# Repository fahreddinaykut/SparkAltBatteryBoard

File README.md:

# SparkAltBatteryBoard

A custom research-oriented battery interface and telemetry board for the DJI Spark platform, built around a standard 3S LiPo battery pack instead of the discontinued, hard-to-find OEM Smart Battery.

This project documents a reverse-engineered I2C/SMBus smart-battery communication interface, originally developed to study how the DJI Spark flight controller communicates with its battery pack. The board sits between a standard 3S pack and the drone, reads the real cell voltages and current, and reproduces that communication interface.

## How it works

1. The original DJI Spark Smart Battery was disassembled and its I2C/SMBus traffic with the flight controller was captured with a Saleae Logic Analyzer.
2. That traffic was decoded to recover the SBS + DJI-proprietary command set (auth handshake, cell voltages, PEC/CRC-8, etc.) — see [`Docs/I2C_BMS_PROTOCOL.md`](Docs/I2C_BMS_PROTOCOL.md).
3. A custom PCB replicates the OEM battery's form factor and connector, with resistor dividers for per-cell voltage sensing and an INA199 current shunt amplifier.
4. An ATmega328P on the board reproduces the Smart Battery communication interface over I2C in real time — computing PEC on the fly and clock-stretching where needed. See [`Firmware/README.md`](Firmware/README.md) for the full protocol implementation.

## Repository structure

| Folder | Contents |
|---|---|
| [`Hardware/`](Hardware) | KiCad project: schematics, PCB layout, 3D connector models, Gerbers, BOM |
| [`Firmware/`](Firmware) | PlatformIO project for the ATmega328P I2C/SMBus battery emulator |
| [`Mechanical/`](Mechanical) | Battery mount 3D model (STEP) |
| [`Docs/`](Docs) | Schematic PDF, protocol reverse-engineering notes, raw sniffed I2C sessions, reference photos/video |

## Hardware

| Top | Bottom | Layout |
|---|---|---|
|  |  |  |

- **MCU:** ATmega328P — chosen specifically because its hardware TWI peripheral supports I2C clock stretching reliably, which the DJI FC's polling requires (see [`Firmware/README.md`](Firmware/README.md#hardware) for why an ESP32 doesn't work here).
- **Sensing:** 3-way resistor divider network for per-cell voltage taps, INA199 shunt amplifier for pack current.
- **Full schematic:** [`Docs/SparkAltBatteryBoardV1.pdf`](Docs/SparkAltBatteryBoardV1.pdf)
- **Fabrication outputs:** [BOM](Hardware/Fabrication/SparkAltBatteryBoard_BOM.csv) · [Gerbers](Hardware/Fabrication/SparkAltBatteryBoard_Gerbers.zip)
- **Battery mount:** [`Mechanical/batterymount.stp`](Mechanical/batterymount.stp)

### PCB Design / Manufacturing Notes

The PCB revision was prepared as a manufacturing-oriented KiCad project, not only as a proof-of-concept schematic.

Design considerations include:

- Hierarchical schematic structure
- Separated MCU, power, sensing, and connector blocks
- 3.3 V I2C/SMBus logic interface
- ADC-scaled cell-voltage sensing inputs
- RC filtering on analog measurement lines
- INA199 high-side current-sense frontend
- Kelvin-style shunt measurement routing approach
- Buck-regulated 3.3 V system rail
- I2C pull-up resistors
- ESD/TVS protection on external communication lines
- AVR ICSP programming/debug header
- Wide copper routing/polygon strategy for battery current path
- Manufacturing outputs prepared: BOM and Gerber package

## Firmware

PlatformIO project targeting the ATmega328P (Arduino Uno/Nano pinout). Handles the I2C slave logic, ADC reads, CRC-8 PEC calculation, and all SBS/DJI command responses.

```
pio run -e uno
pio run -e uno -t upload
```

Full pin map, supported command table, and known limitations: [`Firmware/README.md`](Firmware/README.md).

## Protocol reverse engineering

The raw logic analyzer captures used to decode the protocol are included for reference:

- [`Docs/sniffedsession2.csv`](Docs/sniffedsession2.csv)
- [`Docs/sniffedsession3.csv`](Docs/sniffedsession3.csv)
- Full write-up: [`Docs/I2C_BMS_PROTOCOL.md`](Docs/I2C_BMS_PROTOCOL.md)

## Legacy Prototype Flight Test

The video below shows an earlier prototype tested around 4 years ago. It does not represent a flight test of the redesigned PCB revision in this repository.

<video src="Docs/flyingvideo.mp4" controls width="100%" poster="Docs/flyingimage.jpeg">
  Your browser can't play the embedded video — <a href="Docs/flyingvideo.mp4">watch/download it here</a>.
</video>

## Disclaimer

This is a hobbyist reverse-engineering project, shared for educational purposes. Flying with a modified battery/BMS is at your own risk — verify cell voltages, current limits, and wiring yourself before flight. Not affiliated with or endorsed by DJI.

The original prototype was flight-tested in the past. The redesigned PCB revision in this repository has not yet been flight-tested because the original test drone was later damaged in a crash.

## License

Source-available for personal, educational, and research use. Commercial use is not permitted without written permission. See [`LICENSE`](LICENSE) (MIT with Commons Clause).

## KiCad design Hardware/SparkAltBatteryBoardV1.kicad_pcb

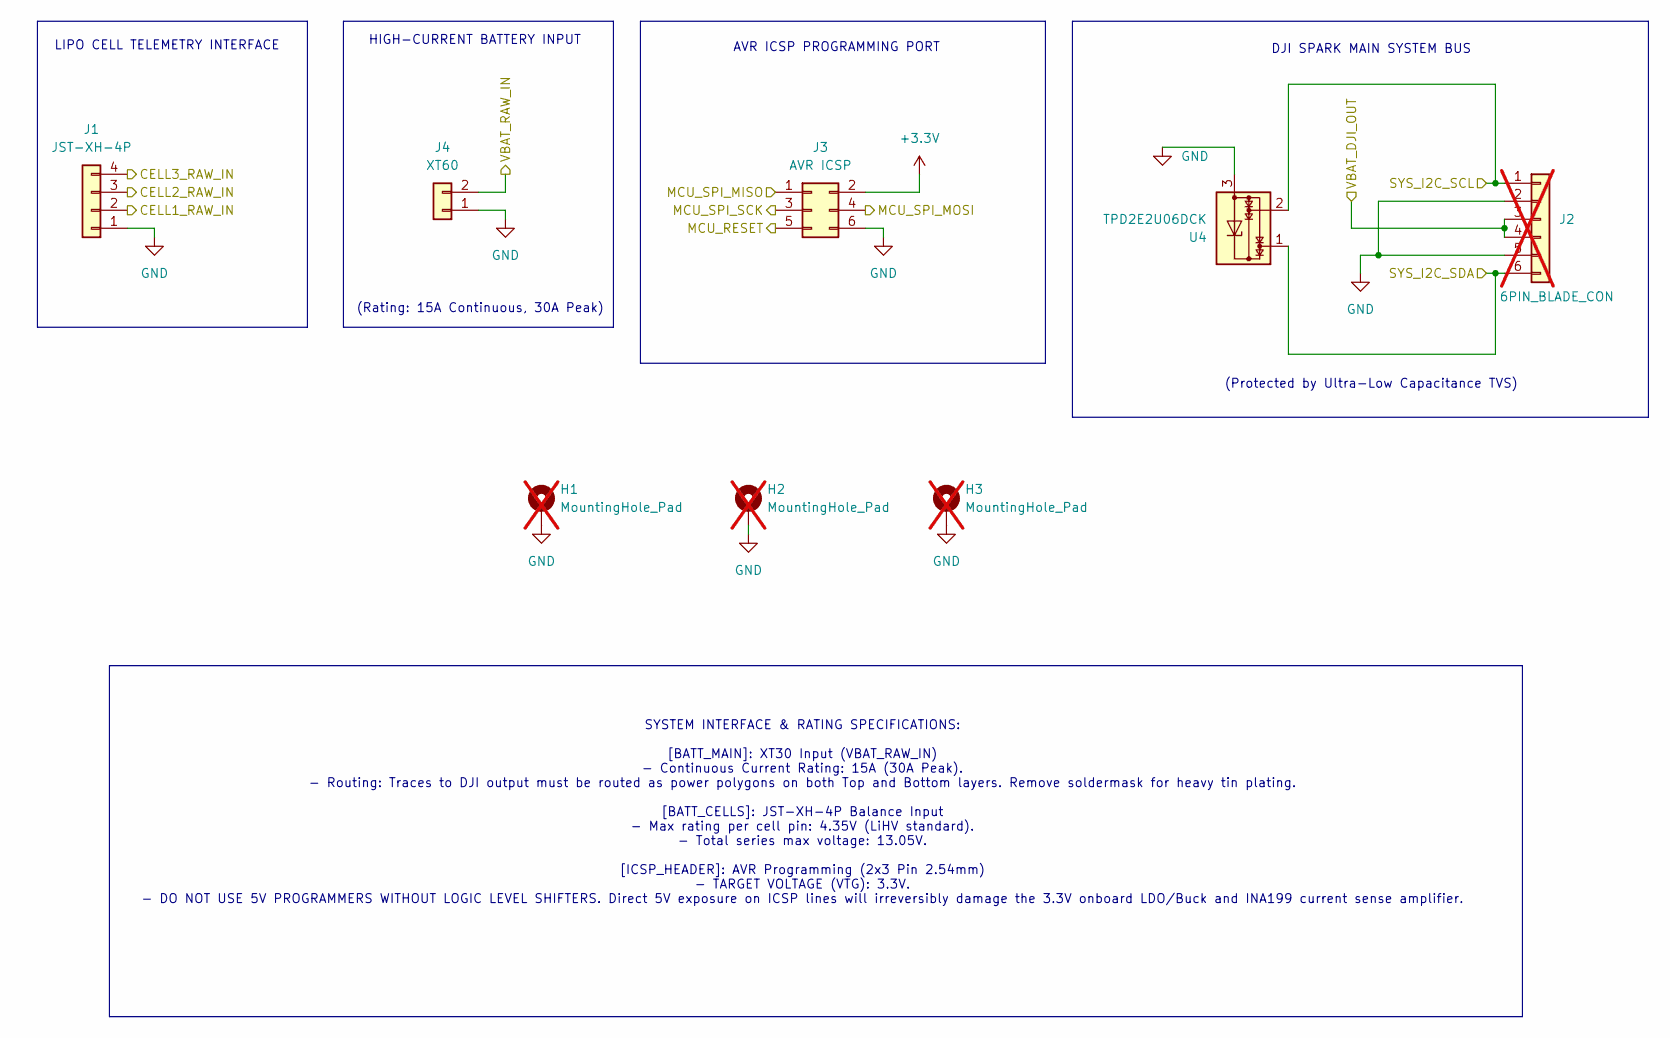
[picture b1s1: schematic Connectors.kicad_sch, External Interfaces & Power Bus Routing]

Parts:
H1, H2, H3: MountingHole_Pad; MountingHole_3.2mm_M3_DIN965_Pad; LCSC Part DNP; not fitted
J1: JST-XH-4P; JST_EH_B4B-EH-A_1x04_P2.50mm_Vertical; LCSC Part C144395
J2: 6PIN_BLADE_CON; Female_Blade_Socket_2mm_6P; LCSC Part DNP; not fitted
J3: AVR ICSP; PinHeader_2x03_P2.54mm_Vertical; LCSC Part C42431837
J4: XT60; AMASS_XT60IPW-M_1x03_P7.20mm_Horizontal; LCSC Part C98732
U4: TPD2E2U06DCK; SOT-323_SC-70; LCSC Part C5350871

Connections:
+3.3V: J3.2; also elsewhere on the board
/Connectors/CELL1_RAW_IN: J1.2; also elsewhere on the board
/Connectors/CELL2_RAW_IN: J1.3; also elsewhere on the board
/Connectors/CELL3_RAW_IN: J1.4; also elsewhere on the board
/Connectors/MCU_RESET: J3.5; also elsewhere on the board
/Connectors/MCU_SPI_MISO: J3.1; also elsewhere on the board
/Connectors/MCU_SPI_MOSI: J3.4; also elsewhere on the board
/Connectors/MCU_SPI_SCK: J3.3; also elsewhere on the board
/MCU_Core/SYS_I2C_SCL: J2.1, U4.2; also elsewhere on the board
/MCU_Core/SYS_I2C_SDA: J2.6, U4.1; also elsewhere on the board
/Power_and_Sensing/ISENSE_N: J2.3, J2.4; also elsewhere on the board
/Power_and_Sensing/ISENSE_P: J4.2; also elsewhere on the board
GND: H1.1 (1_1), H2.1 (1_1), H3.1 (1_1), J1.1, J2.2, J2.5, J3.6, J4.1, U4.3; also elsewhere on the board

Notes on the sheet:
(Rating: 15A Continuous, 30A Peak)
AVR ICSP PROGRAMMING PORT
DJI SPARK MAIN SYSTEM BUS
(Protected by Ultra-Low Capacitance TVS)
LIPO CELL TELEMETRY INTERFACE
SYSTEM INTERFACE & RATING SPECIFICATIONS: [BATT_MAIN]: XT30 Input (VBAT_RAW_IN) - Continuous Current Rating: 15A (30A Peak). - Routing: Traces to DJI output must be routed as power polygons on both Top and Bottom layers. Remove soldermask for heavy tin plating. [BATT_CELLS]: JST-XH-4P Balance Input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
HIGH-CURRENT BATTERY INPUT

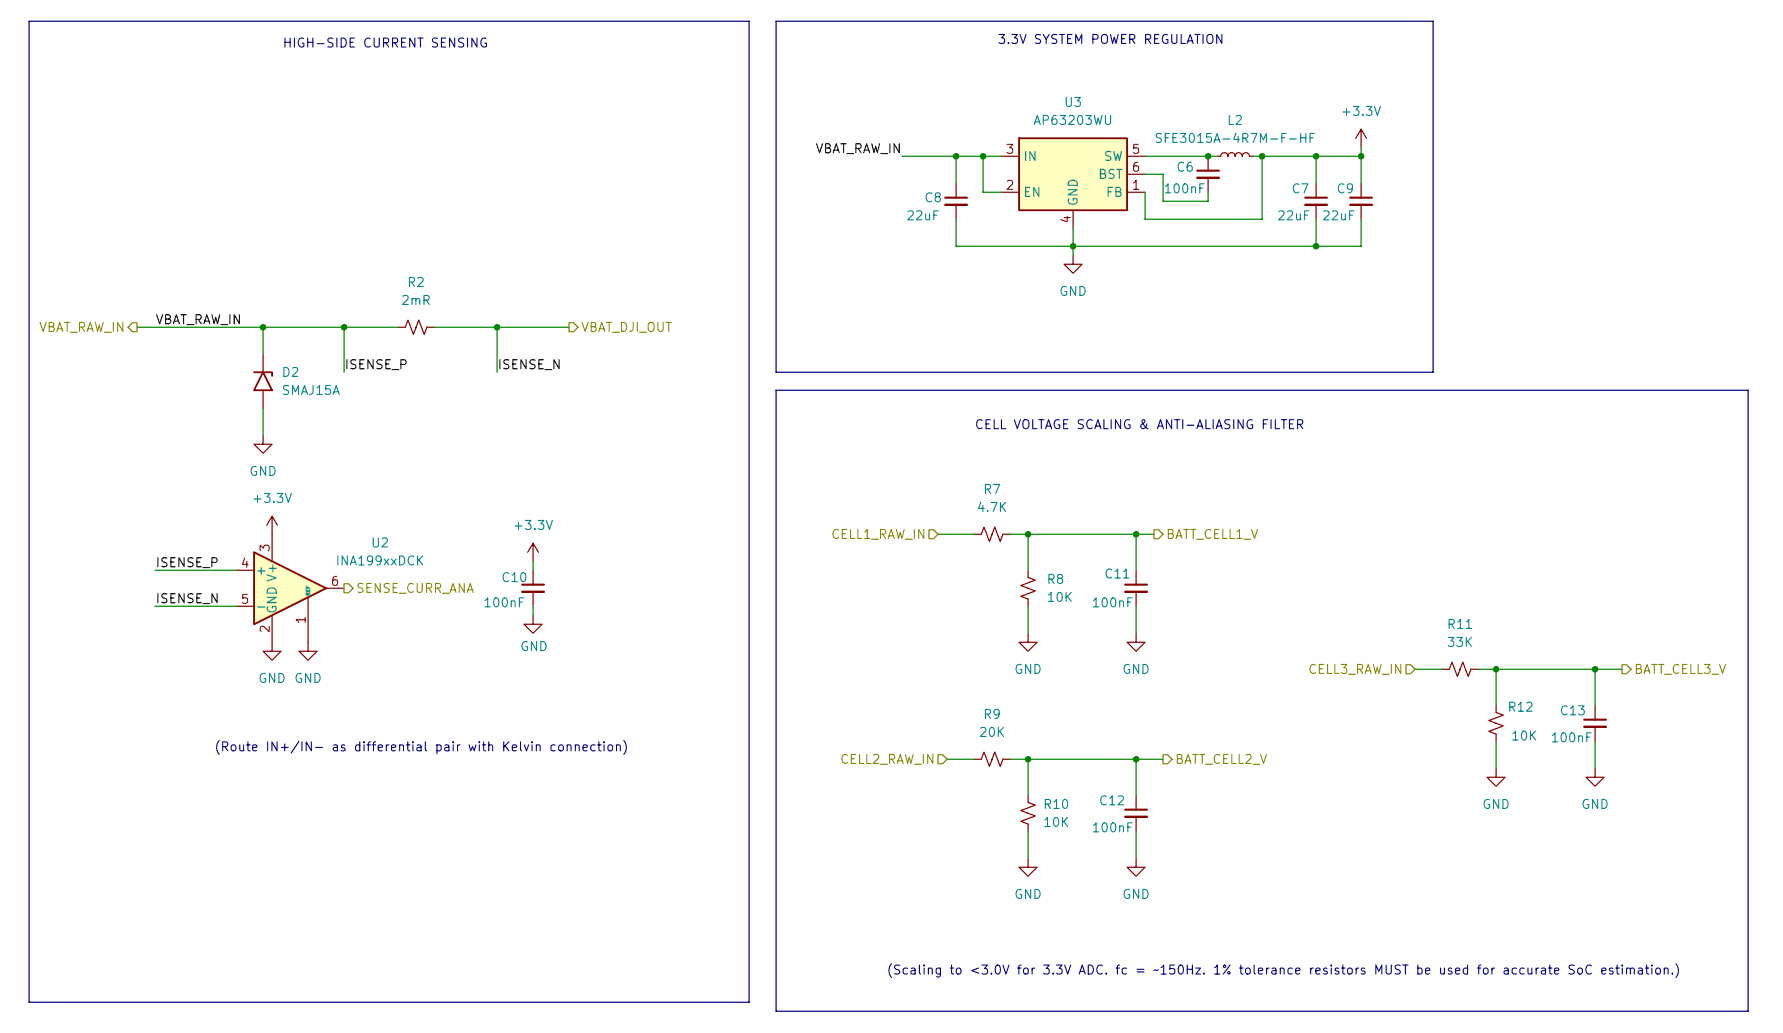
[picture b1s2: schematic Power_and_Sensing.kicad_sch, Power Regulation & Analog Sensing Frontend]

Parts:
C6, C10, C11, C12, C13: 100nF; C_0603_1608Metric; LCSC Part C235731
C7, C8, C9: 22uF; C_0805_2012Metric; LCSC Part C33546009
D2: SMAJ15A; D_SMA; LCSC Part C19077535
L2: SFE3015A-4R7M-F-HF; L_Coilcraft_LPS3010; LCSC Part C5159666
R2: 2mR; R_1206_3216Metric; LCSC Part C49164932
R7: 4.7K; R_0603_1608Metric; LCSC Part C163914
R8, R10, R12: 10K; R_0603_1608Metric; LCSC Part C2930027
R9: 20K; R_0603_1608Metric; LCSC Part C2907124
R11: 33K; R_0603_1608Metric; LCSC Part C880143
U2: INA199xxDCK; SOT-363_SC-70-6; LCSC Part C59135
U3: AP63203WU; TSOT-23-6; LCSC Part C780769

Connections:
+3.3V: C7.1, C9.1, C10.1, L2.2, U2.3 (V+), U3.1 (FB); also elsewhere on the board
/Connectors/CELL1_RAW_IN: R7.1; also elsewhere on the board
/Connectors/CELL2_RAW_IN: R9.1; also elsewhere on the board
/Connectors/CELL3_RAW_IN: R11.1; also elsewhere on the board
/MCU_Core/BATT_CELL1_V: C11.1, R7.2, R8.2; also elsewhere on the board
/MCU_Core/BATT_CELL2_V: C12.1, R9.2, R10.2; also elsewhere on the board
/MCU_Core/BATT_CELL3_V: C13.1, R11.2, R12.2; also elsewhere on the board
/MCU_Core/SENSE_CURR_ANA: U2.6; also elsewhere on the board
/Power_and_Sensing/ISENSE_N: R2.2, U2.5 (-); also elsewhere on the board
/Power_and_Sensing/ISENSE_P: C8.1, D2.1 (A1), R2.1, U2.4 (+), U3.2 (EN), U3.3 (IN); also elsewhere on the board
GND: C7.2, C8.2, C9.2, C10.2, C11.2, C12.2, C13.2, D2.2 (A2), R8.1, R10.1, R12.1, U2.1 (REF), U2.2 (GND), U3.4 (GND); also elsewhere on the board
unnamed: C6.2, U3.6 (BST)
unnamed: C6.1, L2.1, U3.5 (SW)

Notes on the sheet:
3.3V SYSTEM POWER REGULATION
(Route IN+/IN- as differential pair with Kelvin connection)
HIGH-SIDE CURRENT SENSING
(Scaling to <3.0V for 3.3V ADC. fc = ~150Hz. 1% tolerance resistors MUST be used for accurate SoC estimation.)
CELL VOLTAGE SCALING & ANTI-ALIASING FILTER

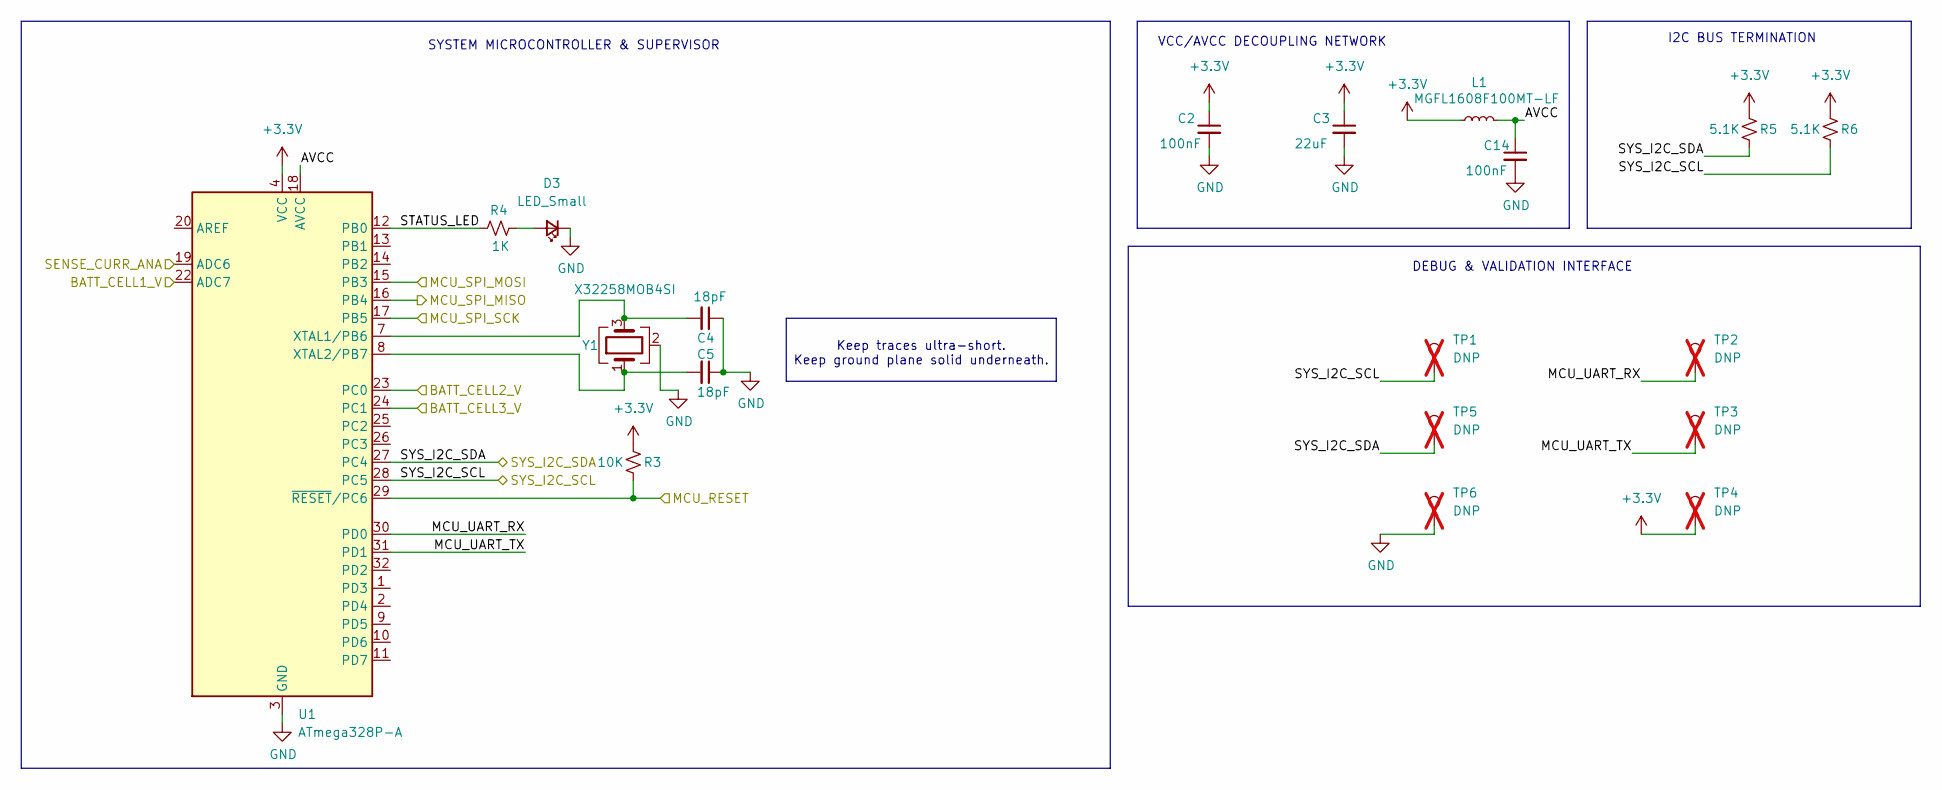
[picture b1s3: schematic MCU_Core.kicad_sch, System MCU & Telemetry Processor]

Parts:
C2, C14: 100nF; C_0603_1608Metric; LCSC Part C235731
C3: 22uF; C_0805_2012Metric; LCSC Part C33546009
C4, C5: 18pF; C_0603_1608Metric; LCSC Part C5137620
D3: LED_Small; LED_0603_1608Metric; LCSC Part C965808
L1: MGFL1608F100MT-LF; L_0603_1608Metric; LCSC Part C281107
R3: 10K; R_0603_1608Metric; LCSC Part C2930027
R4: 1K; R_0603_1608Metric; LCSC Part C2907002
R5, R6: 5.1K; R_0603_1608Metric; LCSC Part C2907044
TP1, TP2, TP3, TP4, TP5, TP6: DNP; TestPoint_Pad_D1.5mm; LCSC Part DNP; not fitted
U1: ATmega328P-A; TQFP-32_7x7mm_P0.8mm; LCSC Part C14877
Y1: X32258MOB4SI; Crystal_SMD_3225-4Pin_3.2x2.5mm; LCSC Part C2682775

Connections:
+3.3V: C2.1, C3.1, L1.1, R3.2, R5.2, R6.2, TP4.1 (1_1), U1.4 (VCC), U1.6 (VCC); also elsewhere on the board
/Connectors/MCU_RESET: R3.1, U1.29 (~RESET/PC6); also elsewhere on the board
/Connectors/MCU_SPI_MISO: U1.16 (PB4); also elsewhere on the board
/Connectors/MCU_SPI_MOSI: U1.15 (PB3); also elsewhere on the board
/Connectors/MCU_SPI_SCK: U1.17 (PB5); also elsewhere on the board
/MCU_Core/AVCC: C14.1, L1.2, U1.18 (AVCC)
/MCU_Core/BATT_CELL1_V: U1.22 (ADC7); also elsewhere on the board
/MCU_Core/BATT_CELL2_V: U1.23 (PC0); also elsewhere on the board
/MCU_Core/BATT_CELL3_V: U1.24 (PC1); also elsewhere on the board
/MCU_Core/MCU_UART_RX: TP2.1 (1_1), U1.30 (PD0)
/MCU_Core/MCU_UART_TX: TP3.1 (1_1), U1.31 (PD1)
/MCU_Core/SENSE_CURR_ANA: U1.19 (ADC6); also elsewhere on the board
/MCU_Core/STATUS_LED: R4.2, U1.12 (PB0)
/MCU_Core/SYS_I2C_SCL: R6.1, TP1.1 (1_1), U1.28 (PC5); also elsewhere on the board
/MCU_Core/SYS_I2C_SDA: R5.1, TP5.1 (1_1), U1.27 (PC4); also elsewhere on the board
GND: C2.2, C3.2, C4.1, C5.1, C14.2, D3.1 (K), TP6.1 (1_1), U1.3 (GND), U1.5 (GND), U1.21 (GND), Y1.2 (G), Y1.4 (G); also elsewhere on the board
unnamed: D3.2 (A), R4.1
unnamed: C4.2, U1.7 (XTAL1/PB6), Y1.3
unnamed: C5.2, U1.8 (XTAL2/PB7), Y1.1

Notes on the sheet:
SYSTEM MICROCONTROLLER & SUPERVISOR
Keep traces ultra-short. Keep ground plane solid underneath.
I2C BUS TERMINATION
VCC/AVCC DECOUPLING NETWORK
DEBUG & VALIDATION INTERFACE

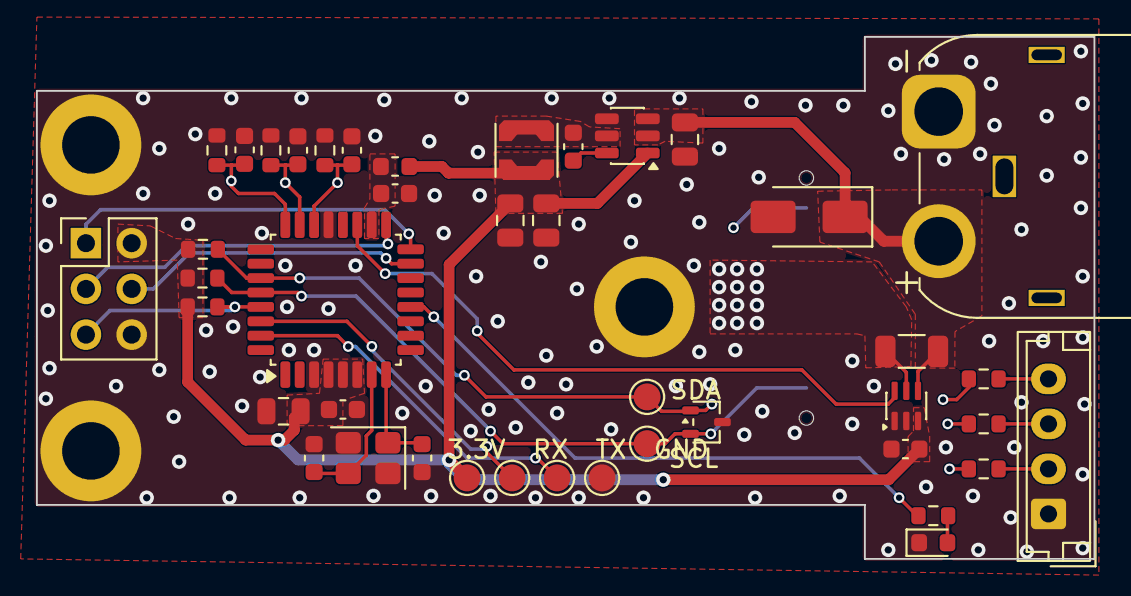
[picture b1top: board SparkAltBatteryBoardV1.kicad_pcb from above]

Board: 4 copper layers, 58.8 x 29.0 mm, 46 parts (1 on the bottom side), 26 nets.

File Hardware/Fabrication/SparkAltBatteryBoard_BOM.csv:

"Reference","Qty","Value","DNP","Footprint","LCSC Part"
"C2,C6,C10,C11,C12,C13,C14","7","100nF","","Capacitor_SMD:C_0603_1608Metric","C235731"
"C3,C7,C8,C9","4","22uF","","Capacitor_SMD:C_0805_2012Metric","C33546009"
"C4,C5","2","18pF","","Capacitor_SMD:C_0603_1608Metric","C5137620"
"D2","1","SMAJ15A","","Diode_SMD:D_SMA","C19077535"
"D3","1","LED_Small","","LED_SMD:LED_0603_1608Metric","C2682775"
"J1","1","JST-XH-4P","","Connector_JST:JST_EH_B4B-EH-A_1x04_P2.50mm_Vertical","C144395"
"J2","1","6PIN_BLADE_CON","DNP","KardLab:Female_Blade_Socket_2mm_6P","DNP"
"J3","1","AVR ICSP","","Connector_PinHeader_2.54mm:PinHeader_2x03_P2.54mm_Vertical","C42431837"
"J4","1","XT60","","Connector_AMASS:AMASS_XT60IPW-M_1x03_P7.20mm_Horizontal","C98732"
"L1","1","MGFL1608F100MT-LF","","Inductor_SMD:L_0603_1608Metric","C281107"
"L2","1","SFE3015A-4R7M-F-HF","","Inductor_SMD:L_Coilcraft_LPS3010","C5159666"
"R2","1","2mR","","Resistor_SMD:R_1206_3216Metric","C49164932"
"R3,R8,R10,R12","4","10K","","Resistor_SMD:R_0603_1608Metric","C2930027"
"R4","1","1K","","Resistor_SMD:R_0603_1608Metric","C2907002"
"R5,R6","2","5.1K","","Resistor_SMD:R_0603_1608Metric","C2907044"
"R7","1","4.7K","","Resistor_SMD:R_0603_1608Metric","C163914"
"R9","1","20K","","Resistor_SMD:R_0603_1608Metric","C2907124"
"R11","1","33K","","Resistor_SMD:R_0603_1608Metric","C880143"
"TP1,TP2,TP3,TP4,TP5,TP6","6","DNP","DNP","TestPoint:TestPoint_Pad_D1.5mm","DNP"
"U1","1","ATmega328P-A","","Package_QFP:TQFP-32_7x7mm_P0.8mm","C14877"
"U2","1","INA199xxDCK","","Package_TO_SOT_SMD:SOT-363_SC-70-6","C59135"
"U3","1","AP63203WU","","Package_TO_SOT_SMD:TSOT-23-6","C780769"
"U4","1","TPD2E2U06DCK","","Package_TO_SOT_SMD:SOT-323_SC-70","C5350871"
"Y1","1","X32258MOB4SI","","Crystal:Crystal_SMD_3225-4Pin_3.2x2.5mm","C2682775"
